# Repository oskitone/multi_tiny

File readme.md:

# multi_tiny

Thinking about an adapter board to connect multiple ATtiny85s to a single programmer using off-the-shelf DIP parts.

_Incredibly_ work-in-progress.

## Requirements / Goals

- Long ZIF socket for fast engagement on multiple chips simultaneously
- Programming is done on each chip individually
- Each chip can connect to target PCB for manual testing
- Support for both manual chip and auto/digital chip selection
- Indicators for board/chip-level statuses
- ~Chainable

## PCB TODOs

- Reverse address pin switch order
- Fix ZIF footprint. Component pins are larger than regular DIP socket
- Unused row fixture holes are misplaced
- Maybe rethink IO header position

## Open questions / Down the line / Considerations

- Do I really need four discrete, per-chip pins to program? Sharing common pins and only multiplexing the minimum could simplify BOM.
- Standalone operation w/o a big computer. Raspberry Pi? SD card for storing hex?
- Queue system: load ZIF and mark ready for programming. LEDs indicate when they're ready, and they can be removed while other ZIFs are being used.
- Arbitrary pin routing to support other chips, pin counts, and number of chips per socket
- For now, intentionally not pursuing...
  - Chip switching could be done with manual switches instead of multiplexers. They'd be weird and expensive and obviously not digitally controllable.
  - Programming chips in parallel is feasible (and, anecdotally, commonplace) but require extra verification to test.
  - Could skip multiplexers and instead use multiple sets of GPIO for ICSP pins. It moves a a lot of the complexity into software, which might be nice! Cons: heavily coupled to specific tech, connecting to a target PCB less straightforward.
  - I'm using the 28 pin ZIF because that's what I have for programming the ATmega328. 32 and 40 pin ZIFs have wider pin spacings but, if I'm reading correctly, may still work for DIP8 chipss.

## `DATE REV 2503`

### Schematic

### BOM

| Designator | Footprint                                         | Quantity | Designation         |
| ---------- | ------------------------------------------------- | -------- | ------------------- |
| C1 to C7   | C_Disc_D5.0mm_W2.5mm_P5.00mm                      | 7        | .1uF                |
| C8         | CP_Radial_D8.0mm_P3.50mm                          | 1        | 220uF               |
| D1 to D3   | LED_D5.0mm-4_RGB_Staggered_Pins                   | 3        | LED_RKGB            |
| D4 to D13  | LED_D3.0mm                                        | 10       | LED                 |
| J1         | PinHeader_2x03_P2.54mm_Vertical                   | 1        | Conn_02x03_Odd_Even |
| J2         | PinHeader_1x08_P2.54mm_Vertical                   | 1        | Conn_01x08          |
| J3         | DIP-28_W7.62mm_LongPads                           | 1        | 28pin ZIF           |
| J4         | PinHeader_1x17_P2.54mm_Vertical                   | 1        | Conn_01x17          |
| R1 to R3   | R_Axial_DIN0207_L6.3mm_D2.5mm_P10.16mm_Horizontal | 3        | 10k                 |
| R5 to R23  | R_Axial_DIN0207_L6.3mm_D2.5mm_P2.54mm_Vertical    | 19       | 1k                  |
| SW1, SW2   | SW_Slide_SPDT_Straight_CK_OS102011MS2Q            | 2        | SW_SPDT             |
| SW4, SW5   | SW_PUSH_6mm                                       | 2        | SW_SPST             |
| U1 to U4   | DIP-16_W7.62mm_Socket_LongPads                    | 4        | CD4052B             |

## License

Designed by Oskitone. Please support future projects by purchasing from [Oskitone](https://www.oskitone.com/).

Creative Commons Attribution/Share-Alike, all text above must be included in any redistribution. See license.txt for additional details.

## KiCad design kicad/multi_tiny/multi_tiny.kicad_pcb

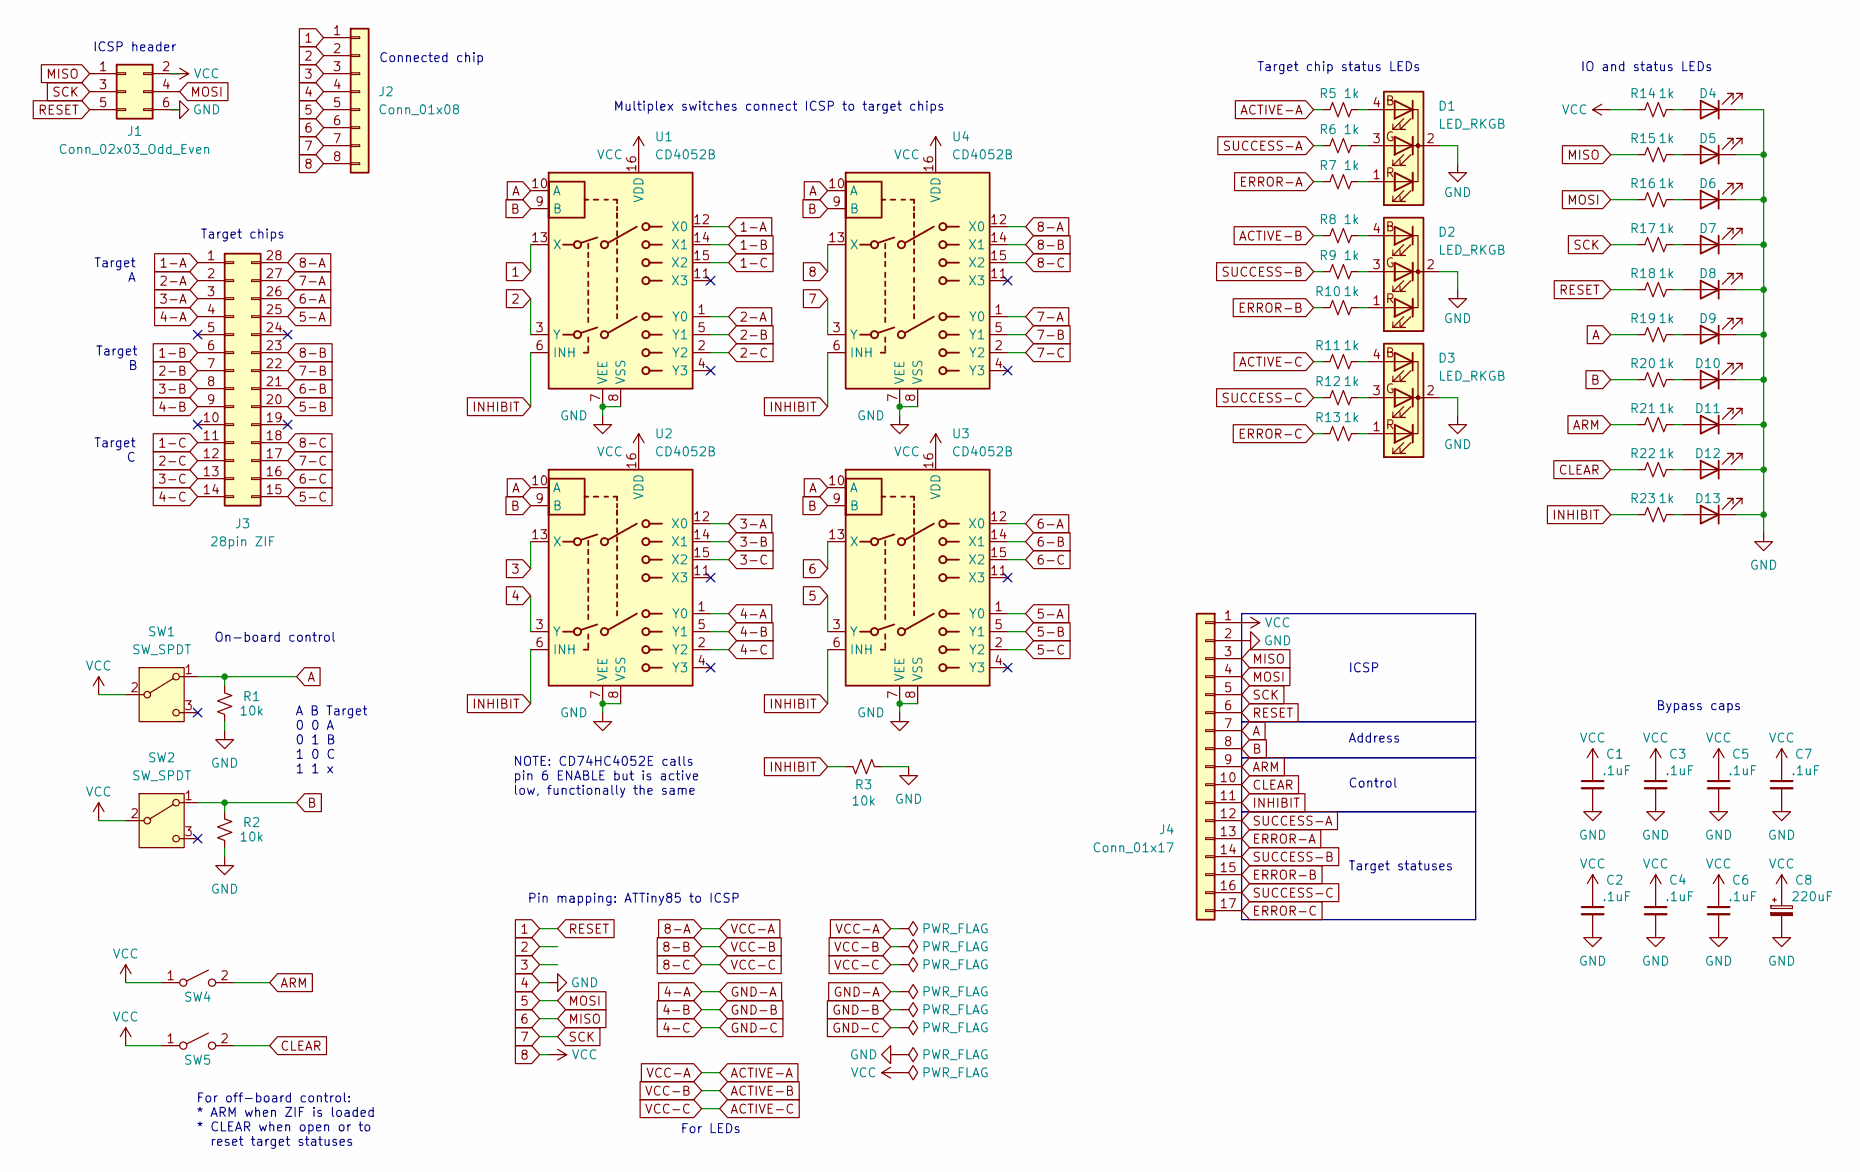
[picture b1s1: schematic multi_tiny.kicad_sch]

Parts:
C1, C2, C3, C4, C5, C6, C7: .1uF; C_Disc_D5.0mm_W2.5mm_P5.00mm
C8: 220uF; CP_Radial_D8.0mm_P3.50mm
D1, D2, D3: LED_RKGB; LED_D5.0mm-4_RGB_Staggered_Pins
D4: VCC; LED_D3.0mm
D5: MISO; LED_D3.0mm
D6: MOSI; LED_D3.0mm
D7: SCK; LED_D3.0mm
D8: RESET; LED_D3.0mm
D9: A; LED_D3.0mm
D10: B; LED_D3.0mm
D11: ARM; LED_D3.0mm
D12: CLEAR; LED_D3.0mm
D13: INHIBIT; LED_D3.0mm
J1: Conn_02x03_Odd_Even; PinHeader_2x03_P2.54mm_Vertical
J2: Conn_01x08; PinHeader_1x08_P2.54mm_Vertical
J3: 28pin ZIF; DIP-28_W7.62mm_LongPads
J4: Conn_01x17; PinHeader_1x17_P2.54mm_Vertical
R1, R2, R3: 10k; R_Axial_DIN0207_L6.3mm_D2.5mm_P10.16mm_Horizontal
R5, R6, R7, R8, R9, R10, R11, R12, R13, R14, R15, R16, R17, R18, R19, R20, R21, R22, R23: 1k; R_Axial_DIN0207_L6.3mm_D2.5mm_P2.54mm_Vertical
SW1, SW2: SW_SPDT; SW_Slide_SPDT_Straight_CK_OS102011MS2Q
SW4, SW5: SW_SPST; SW_PUSH_6mm
U1, U2, U3, U4: CD4052B; DIP-16_W7.62mm_Socket_LongPads

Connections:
1: J1.5, J2.1, J4.6, R18.1, U1.13 (X)
1-A: J3.1, U1.12 (X0)
1-B: J3.6, U1.14 (X1)
1-C: J3.11, U1.15 (X2)
2: J2.2, U1.3 (Y)
2-A: J3.2, U1.1 (Y0)
2-B: J3.7, U1.5 (Y1)
2-C: J3.12, U1.2 (Y2)
3: J2.3, U2.13 (X)
3-A: J3.3, U2.12 (X0)
3-B: J3.8, U2.14 (X1)
3-C: J3.13, U2.15 (X2)
4: C1.2, C2.2, C3.2, C4.2, C5.2, C6.2, C7.2, C8.2, D1.2 (K), D2.2 (K), D3.2 (K), D4.1 (K), D5.1 (K), D6.1 (K), D7.1 (K), D8.1 (K), D9.1 (K), D10.1 (K), D11.1 (K), D12.1 (K), D13.1 (K), J1.6, J2.4, J4.2, R1.1, R2.1, R3.1, U1.7 (VEE), U1.8 (VSS), U2.3 (Y), U2.7 (VEE), U2.8 (VSS), U3.7 (VEE), U3.8 (VSS), U4.7 (VEE), U4.8 (VSS)
4-A: J3.4, U2.1 (Y0)
4-B: J3.9, U2.5 (Y1)
4-C: J3.14, U2.2 (Y2)
5: J1.4, J2.5, J4.4, R16.1, U3.3 (Y)
5-A: J3.25, U3.1 (Y0)
5-B: J3.20, U3.5 (Y1)
5-C: J3.15, U3.2 (Y2)
6: J1.1, J2.6, J4.3, R15.1, U3.13 (X)
6-A: J3.26, U3.12 (X0)
6-B: J3.21, U3.14 (X1)
6-C: J3.16, U3.15 (X2)
7: J1.3, J2.7, J4.5, R17.1, U4.3 (Y)
7-A: J3.27, U4.1 (Y0)
7-B: J3.22, U4.5 (Y1)
7-C: J3.17, U4.2 (Y2)
8: C1.1, C2.1, C3.1, C4.1, C5.1, C6.1, C7.1, C8.1, J1.2, J2.8, J4.1, R14.1, SW1.2 (B), SW2.2 (B), SW4.1 (A), SW5.1 (A), U1.16 (VDD), U2.16 (VDD), U3.16 (VDD), U4.13 (X), U4.16 (VDD)
8-A: J3.28, R5.1, U4.12 (X0)
8-B: J3.23, R8.1, U4.14 (X1)
8-C: J3.18, R11.1, U4.15 (X2)
A: J4.7, R1.2, R19.1, SW1.1 (A), U1.10 (A), U2.10 (A), U3.10 (A), U4.10 (A)
ARM: J4.9, R21.1, SW4.2 (B)
B: J4.8, R2.2, R20.1, SW2.1 (A), U1.9 (B), U2.9 (B), U3.9 (B), U4.9 (B)
CLEAR: J4.10, R22.1, SW5.2 (B)
ERROR-A: J4.13, R7.1
ERROR-B: J4.15, R10.1
ERROR-C: J4.17, R13.1
INHIBIT: J4.11, R3.2, R23.1, U1.6 (INH), U2.6 (INH), U3.6 (INH), U4.6 (INH)
unnamed: D1.4 (BA), R5.2
unnamed: D1.3 (GA), R6.2
unnamed: D1.1 (RA), R7.2
unnamed: D2.4 (BA), R8.2
unnamed: D2.3 (GA), R9.2
unnamed: D2.1 (RA), R10.2
unnamed: D3.4 (BA), R11.2
unnamed: D3.3 (GA), R12.2
unnamed: D3.1 (RA), R13.2
unnamed: D4.2 (A), R14.2
unnamed: D5.2 (A), R15.2
unnamed: D6.2 (A), R16.2
unnamed: D7.2 (A), R17.2
unnamed: D8.2 (A), R18.2
unnamed: D9.2 (A), R19.2
unnamed: D10.2 (A), R20.2
unnamed: D11.2 (A), R21.2
unnamed: D12.2 (A), R22.2
unnamed: D13.2 (A), R23.2
SUCCESS-A: J4.12, R6.1
SUCCESS-B: J4.14, R9.1
SUCCESS-C: J4.16, R12.1

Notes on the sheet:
Target C
Control
A B Target 0 0 A 0 1 B 1 0 C 1 1 x
Target chips
For off-board control: * ARM when ZIF is loaded * CLEAR when open or to reset target statuses
Connected chip
Address
Pin mapping: ATTiny85 to ICSP
Multiplex switches connect ICSP to target chips
ICSP
IO and status LEDs
Bypass caps
Target chip status LEDs
Target B
ICSP header
NOTE: CD74HC4052E calls pin 6 ENABLE but is active low, functionally the same
Target A
For LEDs
On-board control
Target statuses

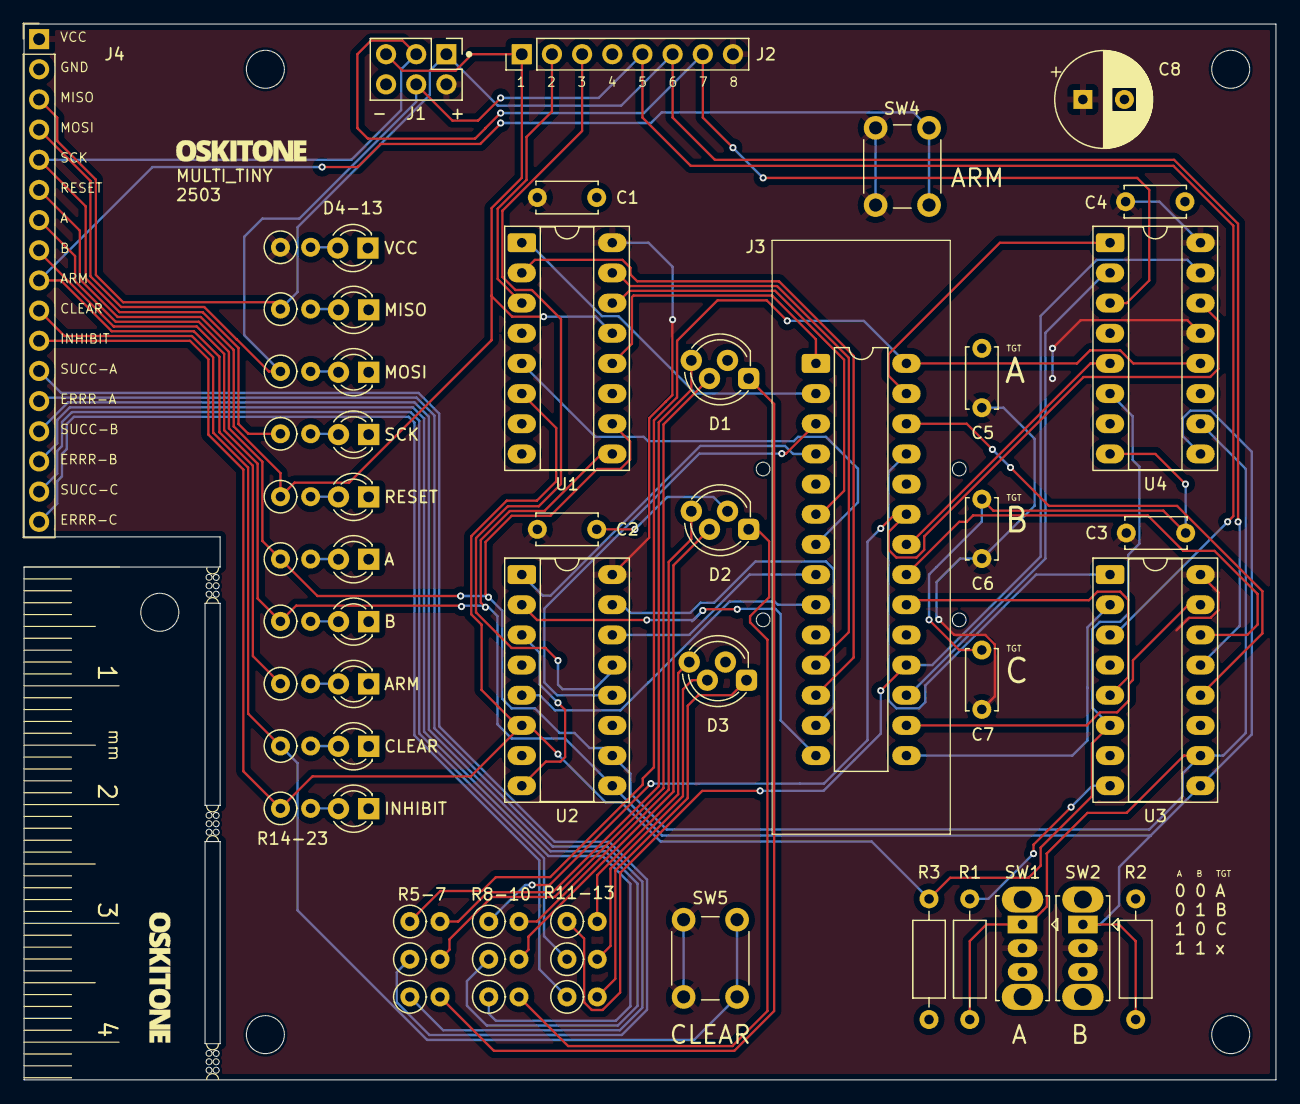
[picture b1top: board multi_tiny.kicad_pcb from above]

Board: 2 copper layers, 105.4 x 88.9 mm, 60 parts (0 on the bottom side), 62 nets.

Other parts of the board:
Ref**: Val**; branding
Ref**#2: Val**; branding
mouse-bite-1mm-3mm, mouse-bite-1mm-3mm#2, mouse-bite-1mm-3mm#3: VAL**; mouse-bite-1mm-3mm

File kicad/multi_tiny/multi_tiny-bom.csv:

"Id";"Designator";"Footprint";"Quantity";"Designation";"Supplier and ref";
1;"U4,U2,U1,U3";"DIP-16_W7.62mm_Socket_LongPads";4;"CD4052B";;;
2;"mouse-bite-1mm-3mm,mouse-bite-1mm-3mm,mouse-bite-1mm-3mm";"mouse-bite-1mm-3mm";3;"VAL**";;;
3;"J1";"PinHeader_2x03_P2.54mm_Vertical";1;"Conn_02x03_Odd_Even";;;
4;"J3";"DIP-28_W7.62mm_LongPads";1;"28pin ZIF";;;
5;"R22,R13,R18,R8,R16,R6,R10,R21,R14,R7,R11,R23,R20,R15,R12,R19,R9,R17,R5";"R_Axial_DIN0207_L6.3mm_D2.5mm_P2.54mm_Vertical";19;"1k";;;
6;"D5";"LED_D3.0mm";1;"MISO";;;
7;"C1,C2,C7,C6,C5,C3,C4";"C_Disc_D5.0mm_W2.5mm_P5.00mm";7;".1uF";;;
8;"SW4,SW5";"SW_PUSH_6mm";2;"SW_SPST";;;
9;"D13";"LED_D3.0mm";1;"INHIBIT";;;
10;"R3,R2,R1";"R_Axial_DIN0207_L6.3mm_D2.5mm_P10.16mm_Horizontal";3;"10k";;;
11;"Ref**,Ref**";"branding";2;"Val**";;;
12;"D9";"LED_D3.0mm";1;"A";;;
13;"D12";"LED_D3.0mm";1;"CLEAR";;;
14;"D6";"LED_D3.0mm";1;"MOSI";;;
15;"J2";"PinHeader_1x08_P2.54mm_Vertical";1;"Conn_01x08";;;
16;"J4";"PinHeader_1x17_P2.54mm_Vertical";1;"Conn_01x17";;;
17;"D1,D3,D2";"LED_D5.0mm-4_RGB_Staggered_Pins";3;"LED_RKGB";;;
18;"SW1,SW2";"SW_Slide_SPDT_Straight_CK_OS102011MS2Q";2;"SW_SPDT";;;
19;"D4";"LED_D3.0mm";1;"VCC";;;
20;"D8";"LED_D3.0mm";1;"RESET";;;
21;"C8";"CP_Radial_D8.0mm_P3.50mm";1;"220uF";;;
22;"D7";"LED_D3.0mm";1;"SCK";;;
23;"D10";"LED_D3.0mm";1;"B";;;
24;"D11";"LED_D3.0mm";1;"ARM";;;

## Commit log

2025-02-22 Start schematic
2025-03-01 Complete MVP schematic
2025-03-02 Swap CD4051 for another CD4052
    * Simplifies BOM
    * Enables arbitrary pin routing later
2025-03-02 Swap chips for ZIF
2025-03-03 Add more IO and organize
2025-03-04 Finalize schematic to start PCB layout
    For now!
    * Merge DIP8 socket into IO header
    * Add "power" LED
    * Rearrange some stuff
    * Assign footprints
2025-03-06 Stub PCB layout
    Schematic changes are mostly for real estate:
    * Combine headers
    * Vertical resistors
2025-03-07 Re-layout for flanked ZIF
2025-03-08 Re-layout
    * Fix ZIF dimensions
    * IO refinements: ditch inhibit switch, pullups
    on external controls, add clear button
2025-03-09 Square PCB
    and put a lil breakaway ruler in the cutout
2025-03-09 Route PCB
    And fix CD4052/target pins arrangement
2025-03-09 Obviate/ignore DRC warnings
2025-03-14 Save ArduinoISP example script
2025-03-14 Clang format
2025-03-16 Extract ArduinoISP
2025-03-23 Fix compilation
2025-03-23 Add BOM CSV
2025-03-24 Stub readme
2026-04-28 Update readme after soldering first PCB rev
    * Add a quick photo
    * Doc TODOs
    A promising start
